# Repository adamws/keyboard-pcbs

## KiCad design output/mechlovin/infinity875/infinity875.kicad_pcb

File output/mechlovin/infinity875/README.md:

## mechlovin/infinity875

[layout](infinity875-kle.json) - [PCB](infinity875.kicad_pcb)

{:loading="lazy"}

[Open in keyboard-layout-editor](http://www.keyboard-layout-editor.com/##@@_x:2.5&c=#777777;&=0,0%0A%0A%0A0,0&_x:1.0&c=#cccccc;&=0,2%0A%0A%0A0,0&=0,3%0A%0A%0A0,0&=0,4%0A%0A%0A0,0&=0,5%0A%0A%0A0,0&_x:0.5&c=#aaaaaa;&=0,6%0A%0A%0A0,0&=0,7%0A%0A%0A0,0&=0,8%0A%0A%0A0,0&=0,9%0A%0A%0A0,0&_x:0.5&c=#cccccc;&=0,10%0A%0A%0A0,0&=0,11%0A%0A%0A0,0&=0,12%0A%0A%0A0,0&=0,13%0A%0A%0A0,0&_x:0.25&c=#aaaaaa;&=0,14&=0,15&=0,16;&@_x:2.5&y:0.25&c=#cccccc;&=1,0&=1,1&=1,2&=1,3&=1,4&=1,5&=1,6&=1,7&=1,8&=1,9&=1,10&=1,11&=1,12&_c=#aaaaaa&w:2;&=1,13%0A%0A%0A1,0&_x:0.25;&=1,14&=1,15&=1,16;&@_x:2.5&w:1.5;&=2,0&_c=#cccccc;&=2,1&=2,2&=2,3&=2,4&=2,5&=2,6&=2,7&=2,8&=2,9&=2,10&=2,11&=2,12&_w:1.5;&=3,12%0A%0A%0A2,0&_x:0.25&c=#aaaaaa;&=2,14&=2,15&=2,16;&@_x:2.5&w:1.75;&=3,0&_c=#cccccc;&=3,1&=3,2&=3,3&=3,4&=3,5&=3,6&=3,7&=3,8&=3,9&=3,10&=3,11&_c=#777777&w:2.25;&=3,13%0A%0A%0A2,0;&@_x:2.5&c=#aaaaaa&w:2.25;&=4,0%0A%0A%0A3,0&_c=#cccccc;&=4,2&=4,3&=4,4&=4,5&=4,6&=4,7&=4,8&=4,9&=4,10&=4,11&_c=#aaaaaa&w:2.75;&=4,13%0A%0A%0A4,0&_x:1.25&c=#777777;&=4,15;&@_x:2.5&c=#aaaaaa&w:1.25;&=5,0%0A%0A%0A5,0&_w:1.25;&=5,1%0A%0A%0A5,0&_w:1.25;&=5,2%0A%0A%0A5,0&_c=#cccccc&w:6.25;&=5,6%0A%0A%0A5,0&_c=#aaaaaa&w:1.25;&=5,10%0A%0A%0A5,0&_w:1.25;&=5,11%0A%0A%0A5,0&_w:1.25;&=5,12%0A%0A%0A5,0&_w:1.25;&=5,13%0A%0A%0A5,0&_x:0.25&c=#777777;&=5,14&=5,15&=5,16;&@_x:21.25&y:-5.0&c=#aaaaaa;&=1,13%0A%0A%0A1,1&=2,13%0A%0A%0A1,1;&@_x:22.0&c=#777777&w:1.25&h:2&w2:1.5&h2:1&x2:-0.25;&=3,13%0A%0A%0A2,1;&@_x:21.0&c=#cccccc;&=3,12%0A%0A%0A2,1;&@_c=#aaaaaa&w:1.25;&=4,0%0A%0A%0A3,1&=4,1%0A%0A%0A3,1&_x:18.75;&=4,12%0A%0A%0A4,1&_w:1.75;&=4,13%0A%0A%0A4,1&_x:0.25&w:1.75;&=4,12%0A%0A%0A4,2&=4,13%0A%0A%0A4,2;&@_x:2.5&y:1.25&c=#777777;&=0,0%0A%0A%0A0,1&_x:0.25&c=#cccccc;&=0,1%0A%0A%0A0,1&=0,2%0A%0A%0A0,1&=0,3%0A%0A%0A0,1&=0,4%0A%0A%0A0,1&_x:0.25&c=#aaaaaa;&=0,5%0A%0A%0A0,1&=0,6%0A%0A%0A0,1&=0,7%0A%0A%0A0,1&=0,8%0A%0A%0A0,1&_x:0.25&c=#cccccc;&=0,9%0A%0A%0A0,1&=0,10%0A%0A%0A0,1&=0,11%0A%0A%0A0,1&=0,12%0A%0A%0A0,1&_x:0.25;&=0,13%0A%0A%0A0,1;&@_x:2.5&y:0.25&c=#aaaaaa&w:1.5;&=5,0%0A%0A%0A5,1&=5,1%0A%0A%0A5,1&_w:1.5;&=5,2%0A%0A%0A5,1&_c=#cccccc&w:7;&=5,6%0A%0A%0A5,1&_c=#aaaaaa&w:1.5;&=5,11%0A%0A%0A5,1&=5,12%0A%0A%0A5,1&_w:1.5;&=5,13%0A%0A%0A5,1)

{:loading="lazy"}

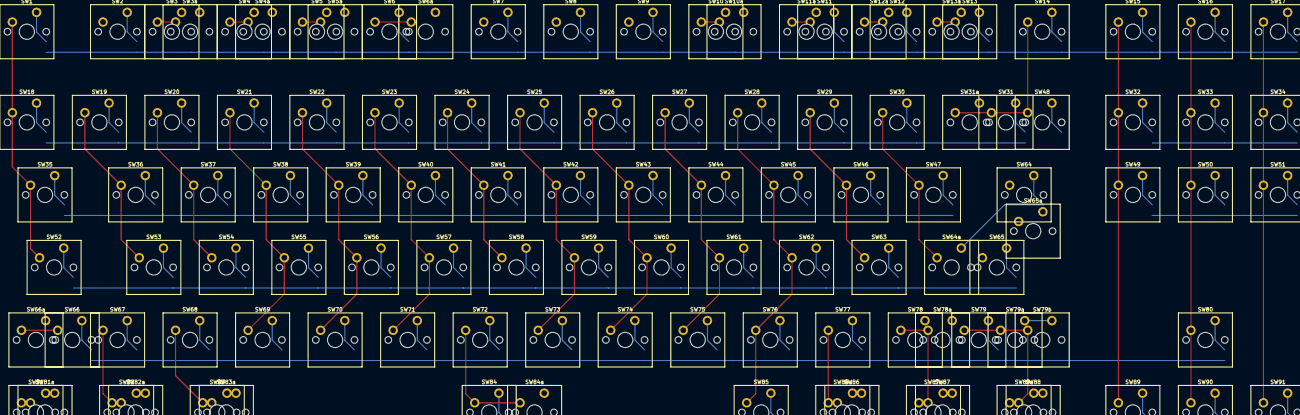
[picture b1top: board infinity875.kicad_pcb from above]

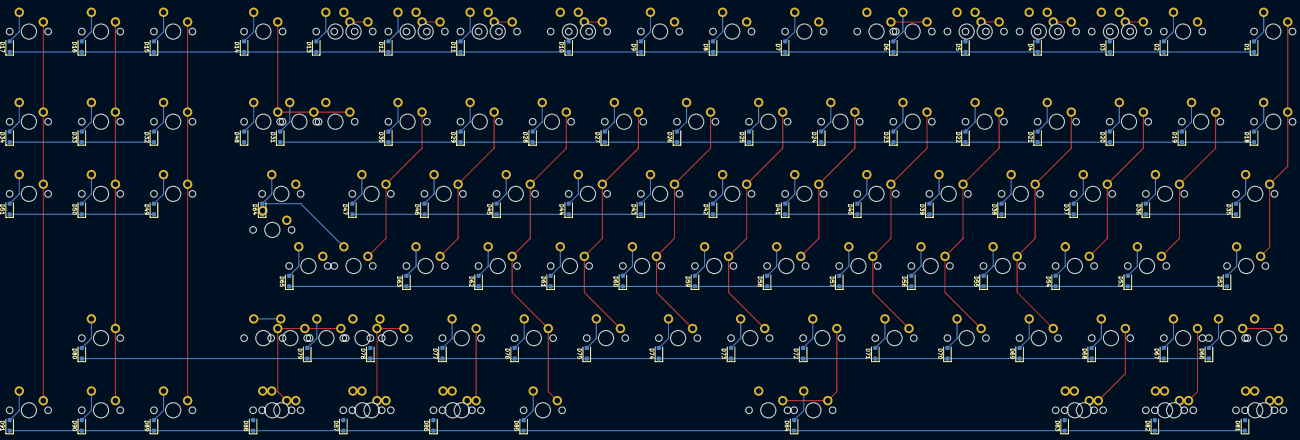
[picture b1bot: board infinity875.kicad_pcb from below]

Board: 2 copper layers, 204 parts (91 on the bottom side), 114 nets.

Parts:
D1, D2, D3, D4, D5, D6, D7, D8, D9, D10, D11, D12, D13, D14, D15, D16, D17, D18, D19, D20, D21, D22, D23, D24, D25, D26, D27, D28, D29, D30, D31, D32, D33, D34, D35, D36, D37, D38, D39, D40, D41, D42, D43, D44, D45, D46, D47, D48, D49, D50, D51, D52, D53, D54, D55, D56, D57, D58, D59, D60, D61, D62, D63, D64, D65, D66, D67, D68, D69, D70, D71, D72, D73, D74, D75, D76, D77, D78, D79, D80, D81, D82, D83, D84, D85, D86, D87, D88, D89, D90, D91: D_SOD-123F
SW1, SW2, SW3, SW3a, SW4, SW4a, SW5, SW5a, SW6, SW6a, SW7, SW8, SW9, SW10, SW10a, SW11, SW11a, SW12, SW12a, SW13, SW13a, SW14, SW15, SW16, SW17, SW18, SW19, SW20, SW21, SW22, SW23, SW24, SW25, SW26, SW27, SW28, SW29, SW30, SW31, SW31a, SW32, SW33, SW34, SW35, SW36, SW37, SW38, SW39, SW40, SW41, SW42, SW43, SW44, SW45, SW46, SW47, SW48, SW49, SW50, SW51, SW52, SW53, SW54, SW55, SW56, SW57, SW58, SW59, SW60, SW61, SW62, SW63, SW64, SW64a, SW65, SW65a, SW66, SW66a, SW67, SW68, SW69, SW70, SW71, SW72, SW73, SW74, SW75, SW76, SW77, SW78, SW78a, SW79, SW79a, SW79b, SW80, SW81, SW81a, SW82, SW82a, SW83, SW83a, SW84, SW84a, SW85, SW86, SW86a, SW87, SW87a, SW88, SW88a, SW89, SW90, SW91: SW_Cherry_MX_PCB_1.00u

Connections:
COL0: SW1.1, SW18.1, SW35.1, SW52.1, SW66.1, SW66a.1, SW81.1, SW81a.1
COL1: SW2.1, SW19.1, SW36.1, SW53.1, SW67.1, SW82.1, SW82a.1
COL2: SW3.1, SW3a.1, SW20.1, SW37.1, SW54.1, SW68.1, SW83.1, SW83a.1
COL3: SW4.1, SW4a.1, SW21.1, SW38.1, SW55.1, SW69.1
COL4: SW5.1, SW5a.1, SW22.1, SW39.1, SW56.1, SW70.1
COL5: SW6.1, SW6a.1, SW23.1, SW40.1, SW57.1, SW71.1
COL6: SW7.1, SW24.1, SW41.1, SW58.1, SW72.1, SW84.1, SW84a.1
COL7: SW8.1, SW25.1, SW42.1, SW59.1, SW73.1
COL8: SW9.1, SW26.1, SW43.1, SW60.1, SW74.1
COL9: SW10.1, SW10a.1, SW27.1, SW44.1, SW61.1, SW75.1
COL10: SW11.1, SW11a.1, SW28.1, SW45.1, SW62.1, SW76.1, SW85.1
COL11: SW12.1, SW12a.1, SW29.1, SW46.1, SW63.1, SW77.1, SW86.1, SW86a.1
COL12: SW13.1, SW13a.1, SW30.1, SW47.1, SW64.1, SW64a.1, SW78.1, SW78a.1, SW87.1, SW87a.1
COL13: SW14.1, SW31.1, SW31a.1, SW48.1, SW65.1, SW65a.1, SW79.1, SW79a.1, SW79b.1, SW88.1, SW88a.1
COL14: SW15.1, SW32.1, SW49.1, SW89.1
COL15: SW16.1, SW33.1, SW50.1, SW80.1, SW90.1
COL16: SW17.1, SW34.1, SW51.1, SW91.1
unnamed: D1.2, SW1.2
unnamed: D2.2, SW2.2
unnamed: D3.2, SW3.2, SW3a.2
unnamed: D4.2, SW4.2, SW4a.2
unnamed: D5.2, SW5.2, SW5a.2
unnamed: D6.2, SW6.2, SW6a.2
unnamed: D7.2, SW7.2
unnamed: D8.2, SW8.2
unnamed: D9.2, SW9.2
unnamed: D10.2, SW10.2, SW10a.2
unnamed: D11.2, SW11.2, SW11a.2
unnamed: D12.2, SW12.2, SW12a.2
unnamed: D13.2, SW13.2, SW13a.2
unnamed: D14.2, SW14.2
unnamed: D15.2, SW15.2
unnamed: D16.2, SW16.2
unnamed: D17.2, SW17.2
unnamed: D18.2, SW18.2
unnamed: D19.2, SW19.2
unnamed: D20.2, SW20.2
unnamed: D21.2, SW21.2
unnamed: D22.2, SW22.2
unnamed: D23.2, SW23.2
unnamed: D24.2, SW24.2
unnamed: D25.2, SW25.2
unnamed: D26.2, SW26.2
unnamed: D27.2, SW27.2
unnamed: D28.2, SW28.2
unnamed: D29.2, SW29.2
unnamed: D30.2, SW30.2
unnamed: D31.2, SW31.2, SW31a.2
unnamed: D32.2, SW32.2
unnamed: D33.2, SW33.2
unnamed: D34.2, SW34.2
unnamed: D35.2, SW35.2
unnamed: D36.2, SW36.2
unnamed: D37.2, SW37.2
unnamed: D38.2, SW38.2
unnamed: D39.2, SW39.2
unnamed: D40.2, SW40.2
unnamed: D41.2, SW41.2
unnamed: D42.2, SW42.2
unnamed: D43.2, SW43.2
unnamed: D44.2, SW44.2
unnamed: D45.2, SW45.2
unnamed: D46.2, SW46.2
unnamed: D47.2, SW47.2
unnamed: D48.2, SW48.2
unnamed: D49.2, SW49.2
unnamed: D50.2, SW50.2
unnamed: D51.2, SW51.2
unnamed: D52.2, SW52.2
unnamed: D53.2, SW53.2
unnamed: D54.2, SW54.2
unnamed: D55.2, SW55.2
unnamed: D56.2, SW56.2
unnamed: D57.2, SW57.2
unnamed: D58.2, SW58.2
unnamed: D59.2, SW59.2
unnamed: D60.2, SW60.2
unnamed: D61.2, SW61.2
unnamed: D62.2, SW62.2
unnamed: D63.2, SW63.2
unnamed: D64.2, SW64.2, SW64a.2
unnamed: D65.2, SW65.2, SW65a.2
unnamed: D66.2, SW66.2, SW66a.2
unnamed: D67.2, SW67.2
unnamed: D68.2, SW68.2
unnamed: D69.2, SW69.2
unnamed: D70.2, SW70.2
unnamed: D71.2, SW71.2
unnamed: D72.2, SW72.2
unnamed: D73.2, SW73.2
unnamed: D74.2, SW74.2
unnamed: D75.2, SW75.2
unnamed: D76.2, SW76.2
unnamed: D77.2, SW77.2
unnamed: D78.2, SW78.2, SW78a.2
unnamed: D79.2, SW79.2, SW79a.2, SW79b.2
unnamed: D80.2, SW80.2
unnamed: D81.2, SW81.2, SW81a.2
unnamed: D82.2, SW82.2, SW82a.2
unnamed: D83.2, SW83.2, SW83a.2
unnamed: D84.2, SW84.2, SW84a.2
unnamed: D85.2, SW85.2
unnamed: D86.2, SW86.2, SW86a.2
unnamed: D87.2, SW87.2, SW87a.2
unnamed: D88.2, SW88.2, SW88a.2
unnamed: D89.2, SW89.2
unnamed: D90.2, SW90.2
unnamed: D91.2, SW91.2
ROW0: D1.1, D2.1, D3.1, D4.1, D5.1, D6.1, D7.1, D8.1, D9.1, D10.1, D11.1, D12.1, D13.1, D14.1, D15.1, D16.1, D17.1
ROW1: D18.1, D19.1, D20.1, D21.1, D22.1, D23.1, D24.1, D25.1, D26.1, D27.1, D28.1, D29.1, D30.1, D31.1, D32.1, D33.1, D34.1
ROW2: D35.1, D36.1, D37.1, D38.1, D39.1, D40.1, D41.1, D42.1, D43.1, D44.1, D45.1, D46.1, D47.1, D48.1, D49.1, D50.1, D51.1
ROW3: D52.1, D53.1, D54.1, D55.1, D56.1, D57.1, D58.1, D59.1, D60.1, D61.1, D62.1, D63.1, D64.1, D65.1
ROW4: D66.1, D67.1, D68.1, D69.1, D70.1, D71.1, D72.1, D73.1, D74.1, D75.1, D76.1, D77.1, D78.1, D79.1, D80.1
ROW5: D81.1, D82.1, D83.1, D84.1, D85.1, D86.1, D87.1, D88.1, D89.1, D90.1, D91.1
